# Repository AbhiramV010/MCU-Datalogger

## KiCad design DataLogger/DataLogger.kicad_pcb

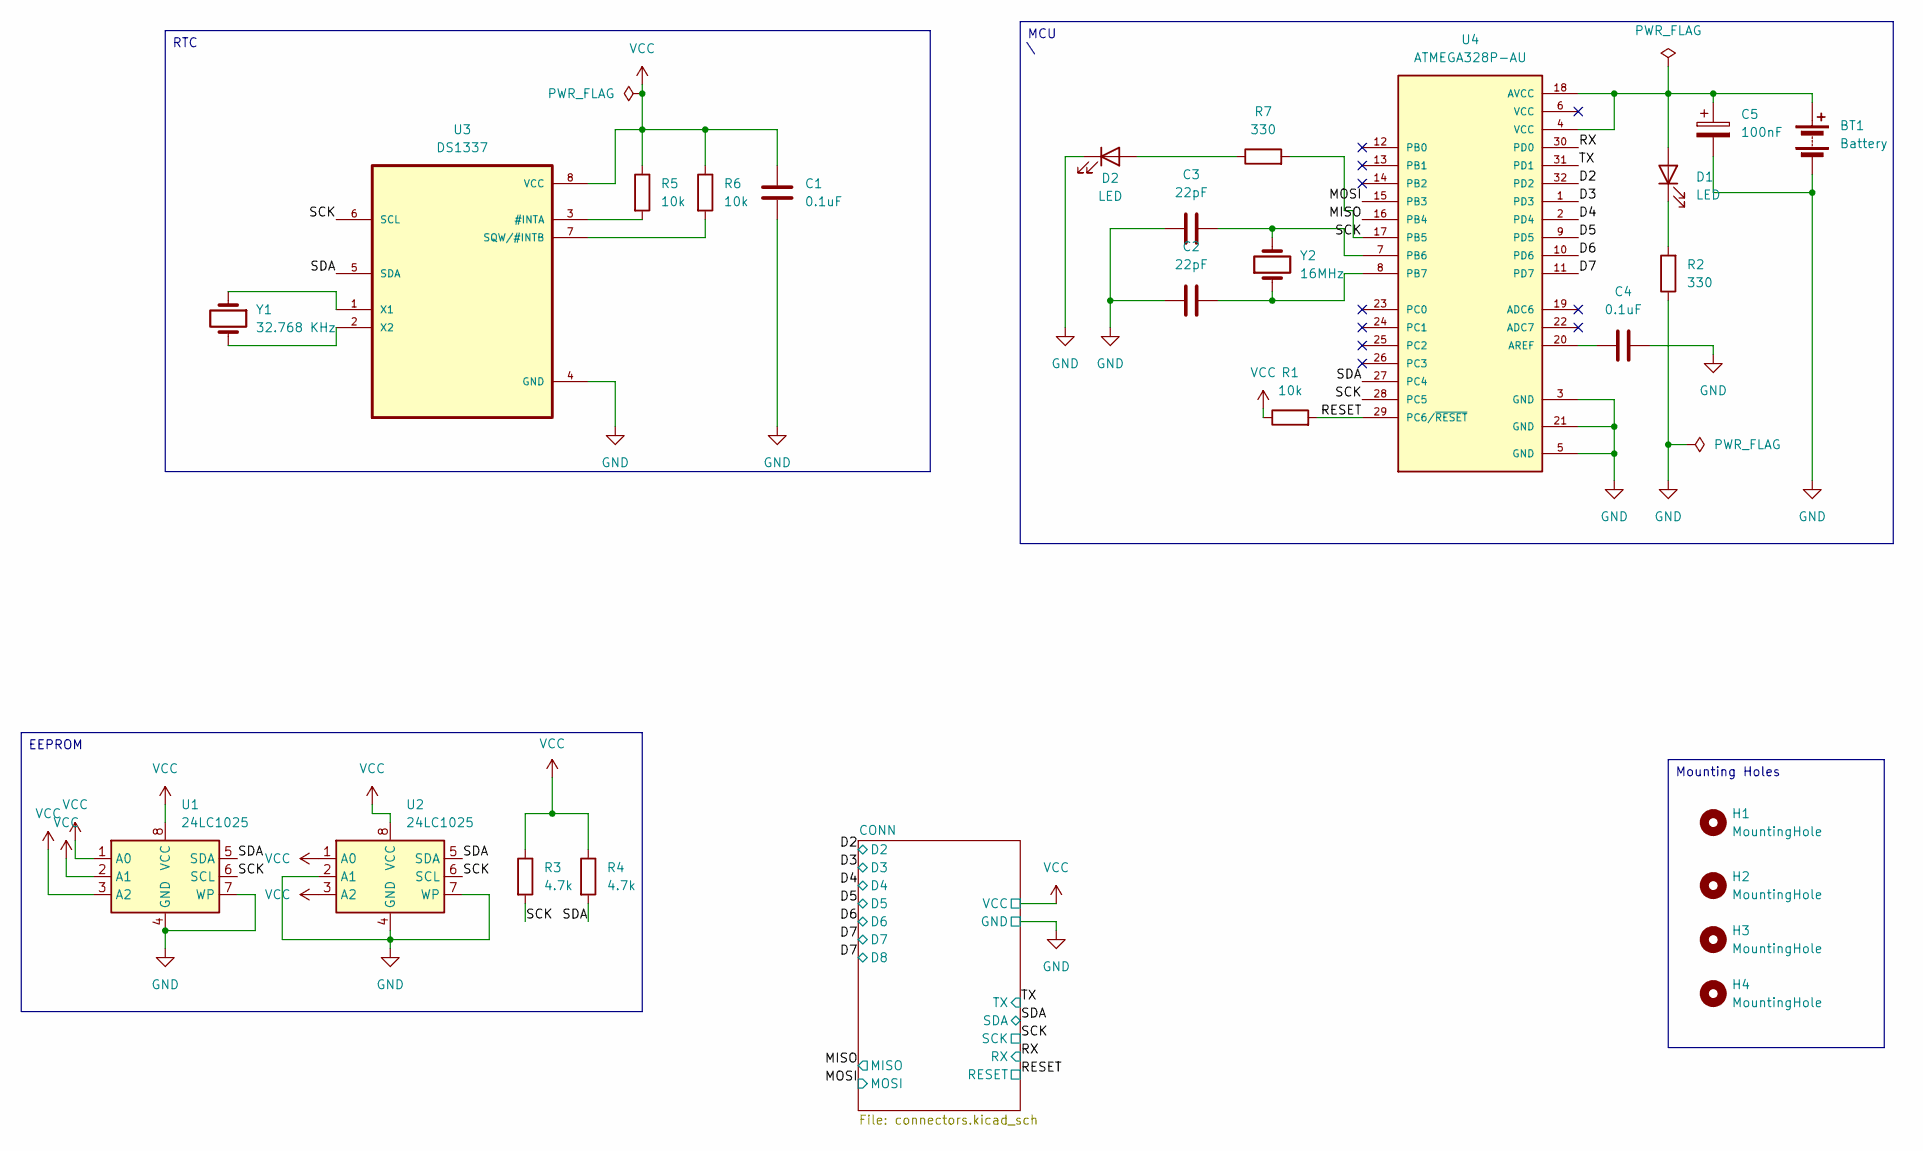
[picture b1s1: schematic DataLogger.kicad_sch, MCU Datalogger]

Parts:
BT1: Battery; BatteryHolder_Keystone_103_1x20mm
C1: 0.1uF; C_1210_3225Metric
C2, C3: 22pF; C_0201_0603Metric
C4: 0.1uF; C_0201_0603Metric
C5: 100nF; CP_Elec_4x3
D1: LED; LED_0201_0603Metric
D2: LED; LED_1210_3225Metric
H1, H2, H3, H4: MountingHole; MountingHole_2.1mm
R1, R5, R6: 10k; R_0805_2012Metric
R2, R7: 330; R_0805_2012Metric
R3, R4: 4.7k; R_0805_2012Metric
U1, U2: 24LC1025; SOIC-8_3.9x4.9mm_P1.27mm
U3: DS1337; SOIC-8_3.9x4.9mm_P1.27mm
U4: ATMEGA328P-AU; TQFP-32_7x7mm_P0.8mm; PARTREV 8271A
Y1: 32.768 KHz; Crystal_SMD_5032-2Pin_5.0x3.2mm
Y2: 16MHz; Crystal_SMD_5032-2Pin_5.0x3.2mm

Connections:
/D2: U4.32 (PD2); also elsewhere on the board
/D3: U4.1 (PD3); also elsewhere on the board
/D4: U4.2 (PD4); also elsewhere on the board
/D5: U4.9 (PD5); also elsewhere on the board
/D6: U4.10 (PD6); also elsewhere on the board
/D7: U4.11 (PD7); also elsewhere on the board
/MISO: U4.16 (PB4); also elsewhere on the board
/MOSI: U4.15 (PB3); also elsewhere on the board
/RESET: R1.2, U4.29 (PC6/~RESET); also elsewhere on the board
/RX: U4.30 (PD0); also elsewhere on the board
/SCK: R3.2, R7.2, U1.6 (SCL), U2.6 (SCL), U3.6 (SCL), U4.17 (PB5), U4.28 (PC5); also elsewhere on the board
/SDA: R4.2, U1.5 (SDA), U2.5 (SDA), U3.5 (SDA), U4.27 (PC4); also elsewhere on the board
/TX: U4.31 (PD1); also elsewhere on the board
GND: BT1.2 (-), C1.2, C2.1, C3.1, C4.2, C5.2, D2.1 (K), R2.1, U1.4 (GND), U1.7 (WP), U2.2 (A1), U2.4 (GND), U2.7 (WP), U3.4 (GND), U4.3 (GND), U4.5 (GND), U4.21 (GND); also elsewhere on the board
unnamed: BT1.1 (+), C5.1, D1.2 (A), U4.4 (VCC), U4.18 (AVCC)
unnamed: D1.1 (K), R2.2
unnamed: D2.2 (A), R7.1
unnamed: R5.2, U3.3 (#INTA)
unnamed: R6.2, U3.7 (SQW/#INTB)
unnamed: U3.1 (X1), Y1.1
unnamed: U3.2 (X2), Y1.2
unnamed: C4.1, U4.20 (AREF)
unnamed: C3.2, U4.7 (PB6), Y2.2
unnamed: C2.2, U4.8 (PB7), Y2.1
VCC: C1.1, R1.1, R3.1, R4.1, R5.1, R6.1, U1.1 (A0), U1.2 (A1), U1.3 (A2), U1.8 (VCC), U2.1 (A0), U2.3 (A2), U2.8 (VCC), U3.8 (VCC); also elsewhere on the board

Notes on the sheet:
EEPROM
Mounting Holes
MCU \
RTC

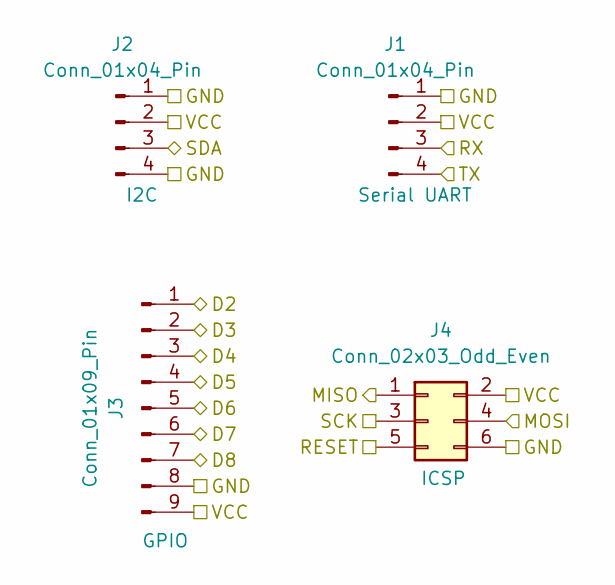
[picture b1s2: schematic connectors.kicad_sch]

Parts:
J1, J2: Conn_01x04_Pin; PinHeader_1x04_P2.54mm_Vertical
J3: Conn_01x09_Pin; PinHeader_1x09_P2.54mm_Vertical
J4: Conn_02x03_Odd_Even; PinHeader_2x03_P2.54mm_Vertical

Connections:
/D2: J3.1; also elsewhere on the board
/D3: J3.2; also elsewhere on the board
/D4: J3.3; also elsewhere on the board
/D5: J3.4; also elsewhere on the board
/D6: J3.5; also elsewhere on the board
/D7: J3.6, J3.7; also elsewhere on the board
/MISO: J4.1; also elsewhere on the board
/MOSI: J4.4; also elsewhere on the board
/RESET: J4.5; also elsewhere on the board
/RX: J1.3; also elsewhere on the board
/SCK: J4.3; also elsewhere on the board
/SDA: J2.3; also elsewhere on the board
/TX: J1.4; also elsewhere on the board
GND: J1.1, J2.1, J2.4, J3.8, J4.6; also elsewhere on the board
VCC: J1.2, J2.2, J3.9, J4.2; also elsewhere on the board

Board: 2 copper layers, 29 parts (0 on the bottom side), 25 nets, no tracks yet.
